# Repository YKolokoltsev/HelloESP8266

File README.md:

# HelloESP8266
This is a minimalistic project aimed to show basic [CMake](https://cmake.org) setup steps required for programming of the ESP8266 chip. The core approach used here was initially based on the [rzajac assembly](https://github.com/rzajac/esp-dev-env.git).  

### Introduction

ESP8266 chip has an Xtensa processor architecture. Xtensa strongly differs from the architectures present in common PC's. It means that compilation of the same C/C++ code would produce absolutely different binaries for your PC and Xtensa. Compilation for the different architecture on the host machine (computer that is used for compilation) is called *cross-compilation*. For many popular microcontroller architectures, for example ARM processors, required cross-compilation tools can be easily installed using system package manager. However, there is no such case yet for ESP8266 implementation of Xtensa.

One of the strongest cross-compilation toolsets known for the moment is [crosstool-NG](https://crosstool-ng.github.io/). This project sopports many architectures including Xtensa, however out of the box ESP8266 support could not be provided by crosstool-NG group because of the flexibility of Xtensa and many variations of it's implementation in different microcontrollers. As a consequence, Max Filippov created a [crosstool-NG fork](https://github.com/jcmvbkbc/crosstool-NG) that was especially oriented to the Xtensa chips including ESP8266. However, even the Max Filippov's project is too generic to start with a concrete chip. It contains just a forked crosstool-NG that is a pure GCC-based compiler and does not include any chip specific API-s. The complete toolset for ESP8266 is collected within [Paul Sokolovsky's open-esp-sdk](https://github.com/pfalcon/esp-open-sdk) project. Clean installation of the open-esp-sdk is the only requirement for HelloESP8266 and this is the point where we start the discussion.

The first step is to clone this project to you local drive:
```
git clone https://github.com/YKolokoltsev/HelloESP8266.git && cd HelloESP8266
```

### Manual compilation of the open-esp-sdk 

Open-esp-sdk is distributed as a source code and shell be compiled before it's usage. It's compilation can be not a trivial task for different Linux distributions (MacOS and Windows are not considered for the moment). An example of it's installation for Debian/Ubuntu families is present at [open-esp-sdk project page](https://github.com/pfalcon/esp-open-sdk). However it may depend on the operating system version. For this reason we support two different scenario of the open-esp-sdk installation. The first one and the most desirable - is the manual compilation of the open-esp-sdk on the host machine. If it was successful, just create a symlink called `open-esp-sdk` within HelloESP8266 cloned folder that points onto the open-esp-sdk:

```
ln -s <esp-open-sdk folder> ./esp-open-sdk
``` 

*NOTE*:
As long as `esp-open-sdk` folder is supposed to be inside of a project tree, in CLion it should de excluded:
project_tree->esp-open-sdk->Mark Directory as->Excluded. This operation will speed-up considerably automatic indexing process during each build.

### Open-esp-sdk within a docker container 

It is highly useful to build the toolchain within your linux-box. However, sometimes this process is not trivial due to many dependencies that may be absent within your default package meneger (see the first stage of the Docker file provided by [Larsks](https://hub.docker.com/r/larsks/esp-open-sdk/dockerfile)). Therefore it is proposed the Docker script that permits to make a remote compilation within the docker container. To create a corresponding image you can use the following commands:

```
docker build -t esp-open-sdk docker
docker system prune --force
```

Creating of a docker image is a two stage process, and it requires at least 6 Gb of available space. The compilation takes a long time.

Than you can link a local HelloESP8266 folder where you have executed all previous commands as docker container volume. In this case it is important not to execute the `/bin/bash` command within your docker run because this command already exist in the Dockerfile and it is a `startup-script`.

```
docker run -it -v `pwd`:/opt/HelloESP8266 esp-open-sdk
cmake -S . -B tmp-build
make -C ./tmp-build/ c_01_blink
``` 

After this run the `tmp-build` folder will be created within your project root. This folder will contain two files: `0x00000.bin` and `0x10000.bin`. In this case you can be sure that compilation has passed successfully. These binary files are the firmware for the esp8266 board that will blink it's LED. You can upload them manually into the flash memory using `esptool.py` as it is described [here](https://github.com/espressif/esptool).

### Misc

CLion: Install Serial Port Monitor plugin to read custom debug messages using `os_printf` function: File->Settings->Plugins->Browse repositories->Serial; However be sure you turn off serial monitor each time before flash your chip.

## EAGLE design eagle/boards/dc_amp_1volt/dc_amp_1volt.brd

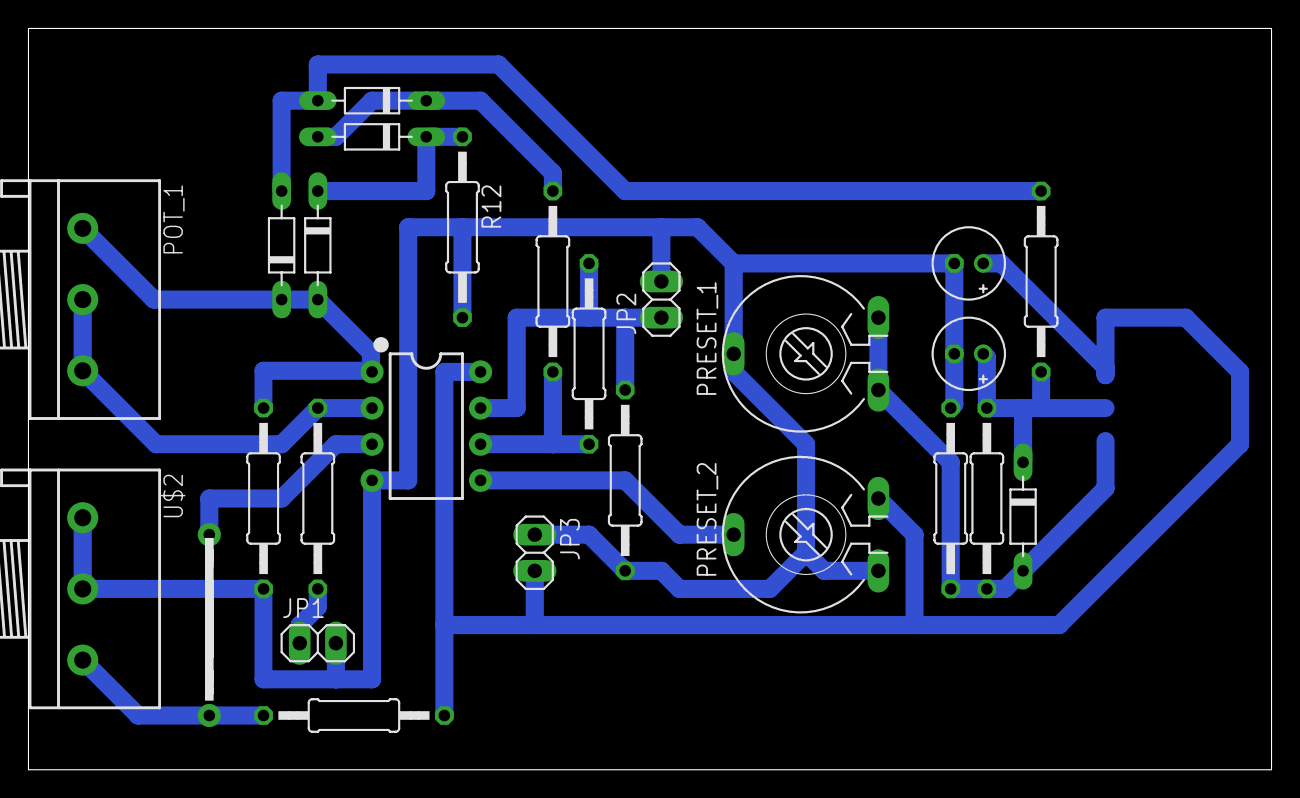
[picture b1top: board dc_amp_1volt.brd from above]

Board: 2 copper layers, 87.3 x 52.1 mm, 27 parts (1 on the bottom side), 14 nets.

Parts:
C1: 10u; E2-5
C2: 22u; E2-5
JP1, JP2, JP3: 1X02
POT_1: POT_1; 3RP/1610N
PRESET_1, PRESET_2: PRESET-10MM; PT-10
R1, R6, R7: 10k; 0207/12
R2, R3: 100k; 0207/12
R4: 220; 0207/12
R5: 20k; 0207/12
R10: 330; 0207/12
R11, R12: 5k; 0207/12
U1: LM358; DIP08
U$1: BRIDGE
U$2: POT_2; 3RP/1610N
U$3: NCP1117; SOT223
U$4, U$6, U$7, U$8, U$9: 1N4148; D-7.5

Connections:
0: C1.-, C2.-, JP1.2, JP2.2, JP3.1, PRESET_1.S, PRESET_2.A, R2.1, R3.1, R10.1, R12.2, U1.4, U$2.1, U$2.2
DC5_L: C1.+, JP3.2, PRESET_2.E, R5.1, U1.8, U$3.3
DC_ADJ_L: C2.+, R4.2, R11.2, U$3.2, U$4.C
IN_L: JP1.1, R1.1
unnamed: R5.2, U1.3, U$1.1, U$1.2, U$2.3
unnamed: PRESET_2.S, U1.5
unnamed: POT_1.2, POT_1.3, R1.2, U1.2
unnamed: R12.1, U$8.C, U$9.C
unnamed: R6.2, R7.1, U1.6
unnamed: R11.1, U$6.A, U$7.A
unnamed: PRESET_1.A, PRESET_1.E, R4.1, R10.2, U$3.1, U$4.A
unnamed: R6.1, U$7.C, U$9.A
OUT: JP2.1, R2.2, R7.2, U1.7
VOUT_1: POT_1.1, R3.2, U1.1, U$6.C, U$8.A

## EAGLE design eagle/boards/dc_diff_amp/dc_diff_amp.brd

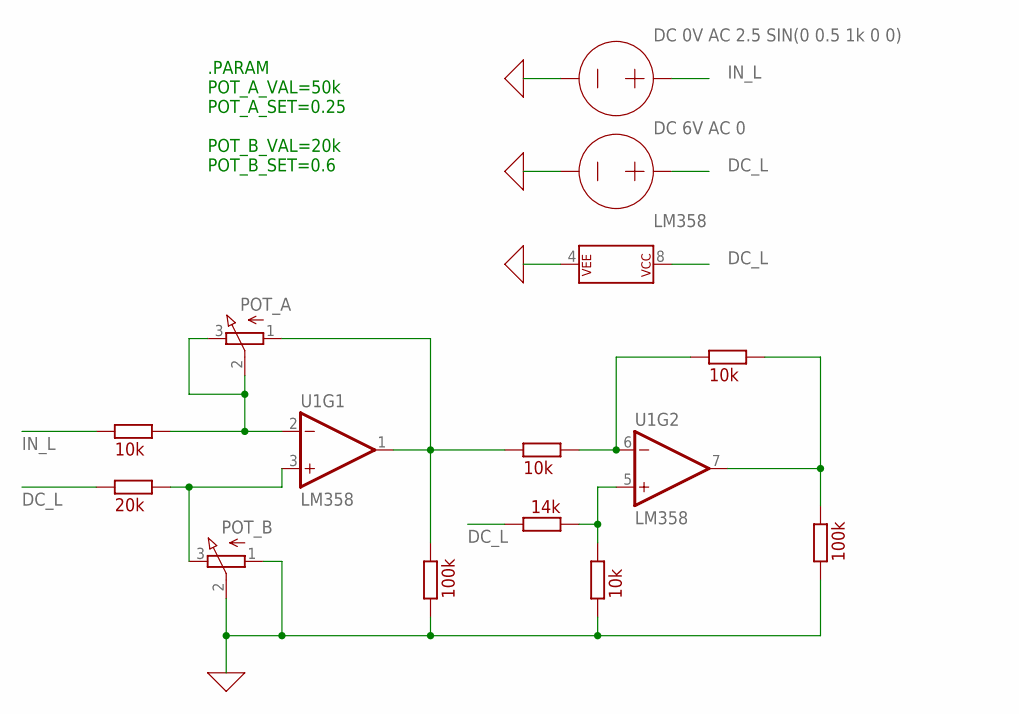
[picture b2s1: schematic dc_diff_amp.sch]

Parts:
R1, R6, R7, R8: 10k; 0207/12
R2, R3: 100k; 0207/12
R5: 20k; 0207/12
R9: 14k; 0207/12
U1: LM358; DIP08
U$1: POT_A; 3RP/1610N
U$2: POT_B; 3RP/1610N

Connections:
0: R2.1, R3.1, R8.1, U1.4 (P$V-), U$2.1 (A), U$2.2 (S)
DC_L: R5.1, R9.2, U1.8 (P$V+)
IN_L: R1.1
unnamed: R5.2, U1.3 (+IN), U$2.3 (E)
unnamed: R8.2, R9.1, U1.5 (+IN)
unnamed: R1.2, U1.2 (-IN), U$1.2 (S), U$1.3 (E)
unnamed: R6.2, R7.1, U1.6 (-IN)
OUT: R2.2, R7.2, U1.7 (OUT)
VOUT_1: R3.2, R6.1, U1.1 (OUT), U$1.1 (A)

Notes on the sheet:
.PARAM POT_A_VAL=50k POT_A_SET=0.25 POT_B_VAL=20k POT_B_SET=0.6

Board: 2 copper layers, 11 parts (0 on the bottom side), 8 nets, no tracks yet.

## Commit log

2019-05-05 Make this project importable in CLion
2019-05-05 Project skeleton created
2019-05-07 Compiation succedded!
2019-05-13 Docker toolset started from scratch
2019-05-14 Find Docker executable
2019-05-14 Script with "docker run" also not working
2019-05-24 Added transferible Docker images for xtensa compiler building
2019-05-24 Updated to single stage Docker
2019-05-25 Improved docks
2019-05-25 Created a remote build scenario
2019-05-25 Empty continuation line recovered
2019-08-20 Compilation options description.
2019-08-20 Merged with docker
2019-08-20 head reset
2019-08-20 Diode blink && Uart on ESP-12F
2019-08-21 Wi-Fi station mode example
2019-08-21 UDP not working, Station need to be rewritten
2019-09-03 C++ build, soft timer on UDP
2019-09-04 Max speeds on UDP, serious lifehack on soft clock
2019-09-09 PATH variable for esptool.py is now automated
2019-09-10 Docker build stage_1 (automatic docker-build folder)
2019-09-20 incuded eagle archives
2019-09-25 DC coupled Amp with limiter + board
2019-09-26 DC Amp. presets added
2019-09-27 eagle library refactored
2019-11-08 Pre-amp board
2019-11-08 ADC with transmission over over UDP
2019-11-09 async ADC with transmission over over UDP
